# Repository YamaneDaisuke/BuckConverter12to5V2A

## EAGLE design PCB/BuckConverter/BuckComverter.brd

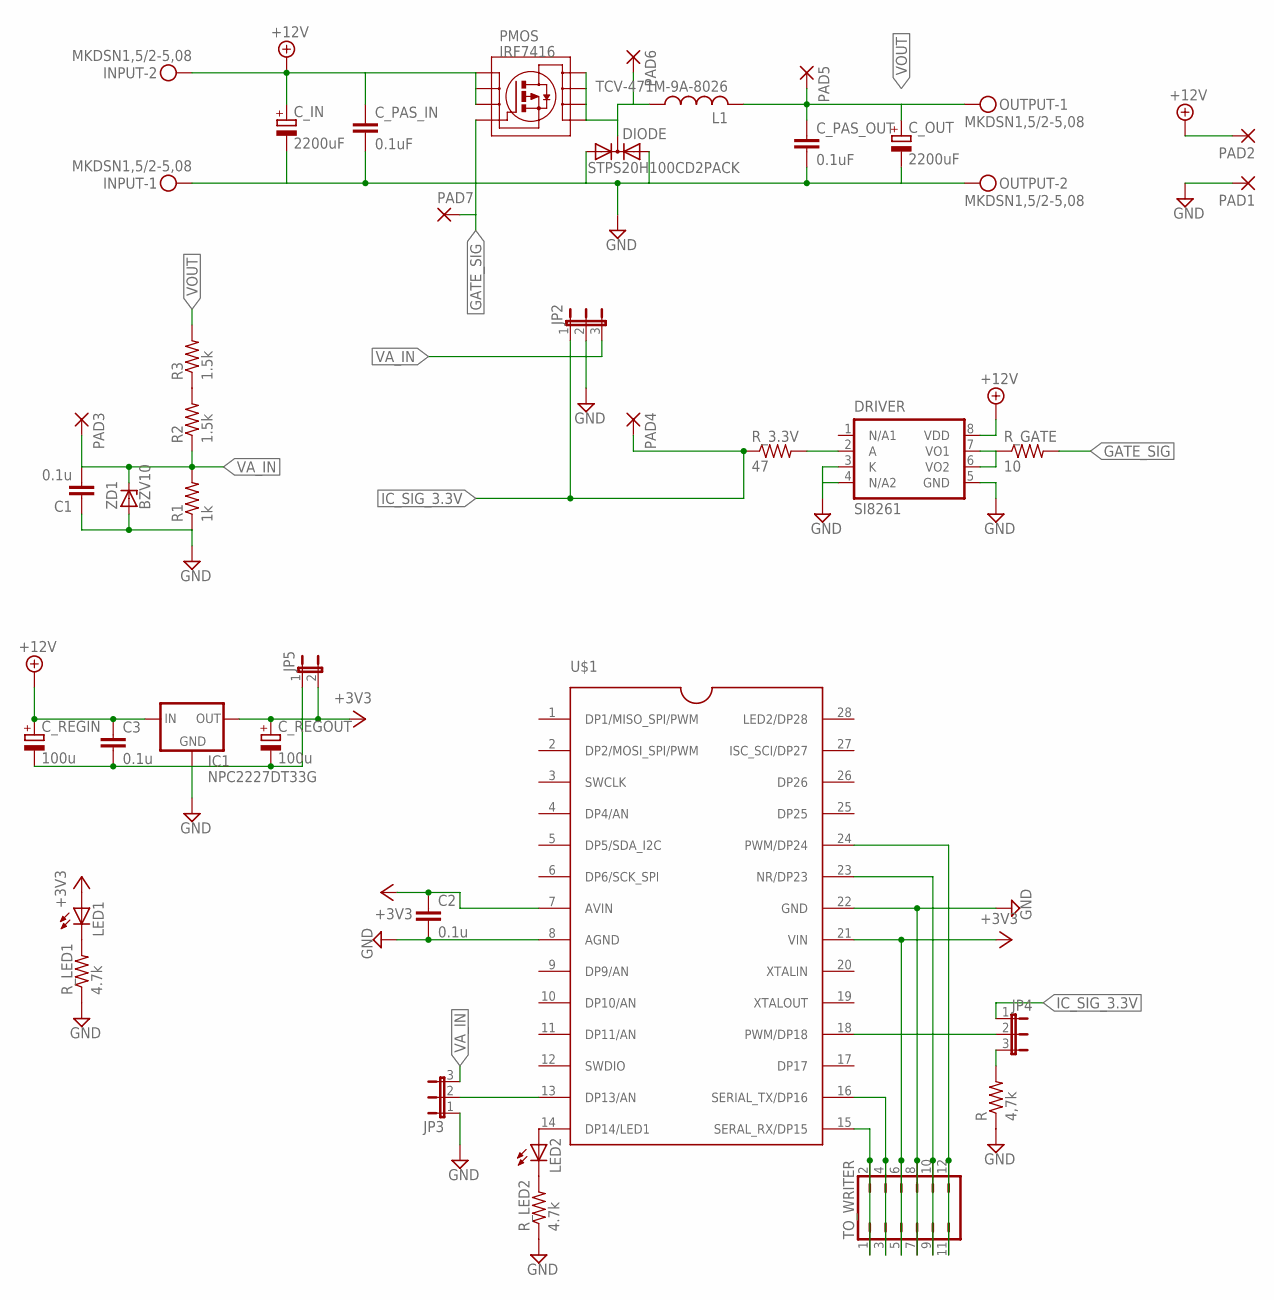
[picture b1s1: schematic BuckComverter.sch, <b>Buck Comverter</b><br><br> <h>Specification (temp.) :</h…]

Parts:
C1, C3: 0.1u; C025-024X044
C2: 0.1u; C2012
C_IN: 2200uF; E7,5-16
C_OUT: 2200uF; E7,5-16
C_PAS_IN: 0.1uF; C3216
C_PAS_OUT: 0.1uF; C3216
C_REGIN: 100u; E2,5-6
C_REGOUT: 100u; E2,5-6
DIODE: STPS20H100CD2PACK; D2PACK
DRIVER: SI8261; SOP08
IC1: NPC2227DT33G; DPACK
INPUT: MKDSN1,5/2-5,08
JP2, JP3, JP4: JP2E; JP2
JP5: JP1E; JP1
L1: TCV-471M-9A-8026
LED1, LED2: LED3MM
OUTPUT: MKDSN1,5/2-5,08
PAD1, PAD2, PAD3, PAD4, PAD5, PAD6, PAD7: 1,6/0,8
PMOS: IRF7416; SOP08
R: 4,7k; 0204/5
R1: 1k; 0207/7
R2: 1.5k; 0207/10
R3: 1.5k; 0207/7
R_3.3V: 47; 0204/7
R_GATE: 10; M2012
R_LED1: 4.7k; 0204V
R_LED2: 4.7k; 0204/7
TO_WRITER: JP6Q
U$1: LPC1114FDH28; TSSOP28
ZD1: BZV10; DO34Z7

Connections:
+3V3: C2.1, C_REGOUT.+, IC1.4 (OUT), JP5.2, LED1.A, TO_WRITER.5, TO_WRITER.6, U$1.7 (AVIN), U$1.21 (VIN)
+12V: C3.1, C_IN.+, C_PAS_IN.1, C_REGIN.+, DRIVER.8 (VDD), IC1.3 (IN), INPUT.2, PAD2.1, PMOS.1 (S1), PMOS.2 (S2), PMOS.3 (S3)
GATE_SIG: PAD7.1, PMOS.4 (G), R_GATE.2
GND: C1.1, C2.2, C3.2, C_IN.-, C_OUT.-, C_PAS_IN.2, C_PAS_OUT.2, C_REGIN.-, C_REGOUT.-, DIODE.1 (A3), DIODE.3 (A4), DRIVER.3 (K), DRIVER.4 (N/A2), DRIVER.5 (GND), IC1.1 (GND), INPUT.1, JP2.2, JP3.1, JP5.1, OUTPUT.2, PAD1.1, R.1, R1.1, R_LED1.1, R_LED2.1, TO_WRITER.7, TO_WRITER.8, U$1.8 (AGND), U$1.22 (GND), ZD1.A
IC_SIG_3.3V: JP2.1, JP4.1, PAD4.1, R_3.3V.1
unnamed: LED1.K (C), R_LED1.2
unnamed: DRIVER.2 (A), R_3.3V.2
unnamed: LED2.A, U$1.14 (DP14/LED1)
unnamed: R2.2, R3.1
unnamed: DRIVER.6 (VO2), DRIVER.7 (VO1), R_GATE.1
unnamed: JP3.2, U$1.13 (DP13/AN)
unnamed: JP4.3, R.2
unnamed: JP4.2, U$1.18 (PWM/DP18)
unnamed: TO_WRITER.1, TO_WRITER.2, U$1.15 (SERAL_RX/DP15)
unnamed: TO_WRITER.3, TO_WRITER.4, U$1.16 (SERIAL_TX/DP16)
unnamed: TO_WRITER.9, TO_WRITER.10, U$1.23 (NR/DP23)
unnamed: TO_WRITER.11, TO_WRITER.12, U$1.24 (PWM/DP24)
unnamed: LED2.K (C), R_LED2.2
unnamed: DIODE.2 (C), L1.P$1 (1), PAD6.1, PMOS.5 (D5), PMOS.6 (D6), PMOS.7 (D7), PMOS.8 (D8)
VA_IN: C1.2, JP2.3, JP3.3, PAD3.1, R1.2, R2.1, ZD1.C
VOUT: C_OUT.+, C_PAS_OUT.1, L1.P$2 (2), OUTPUT.1, PAD5.1, R3.2

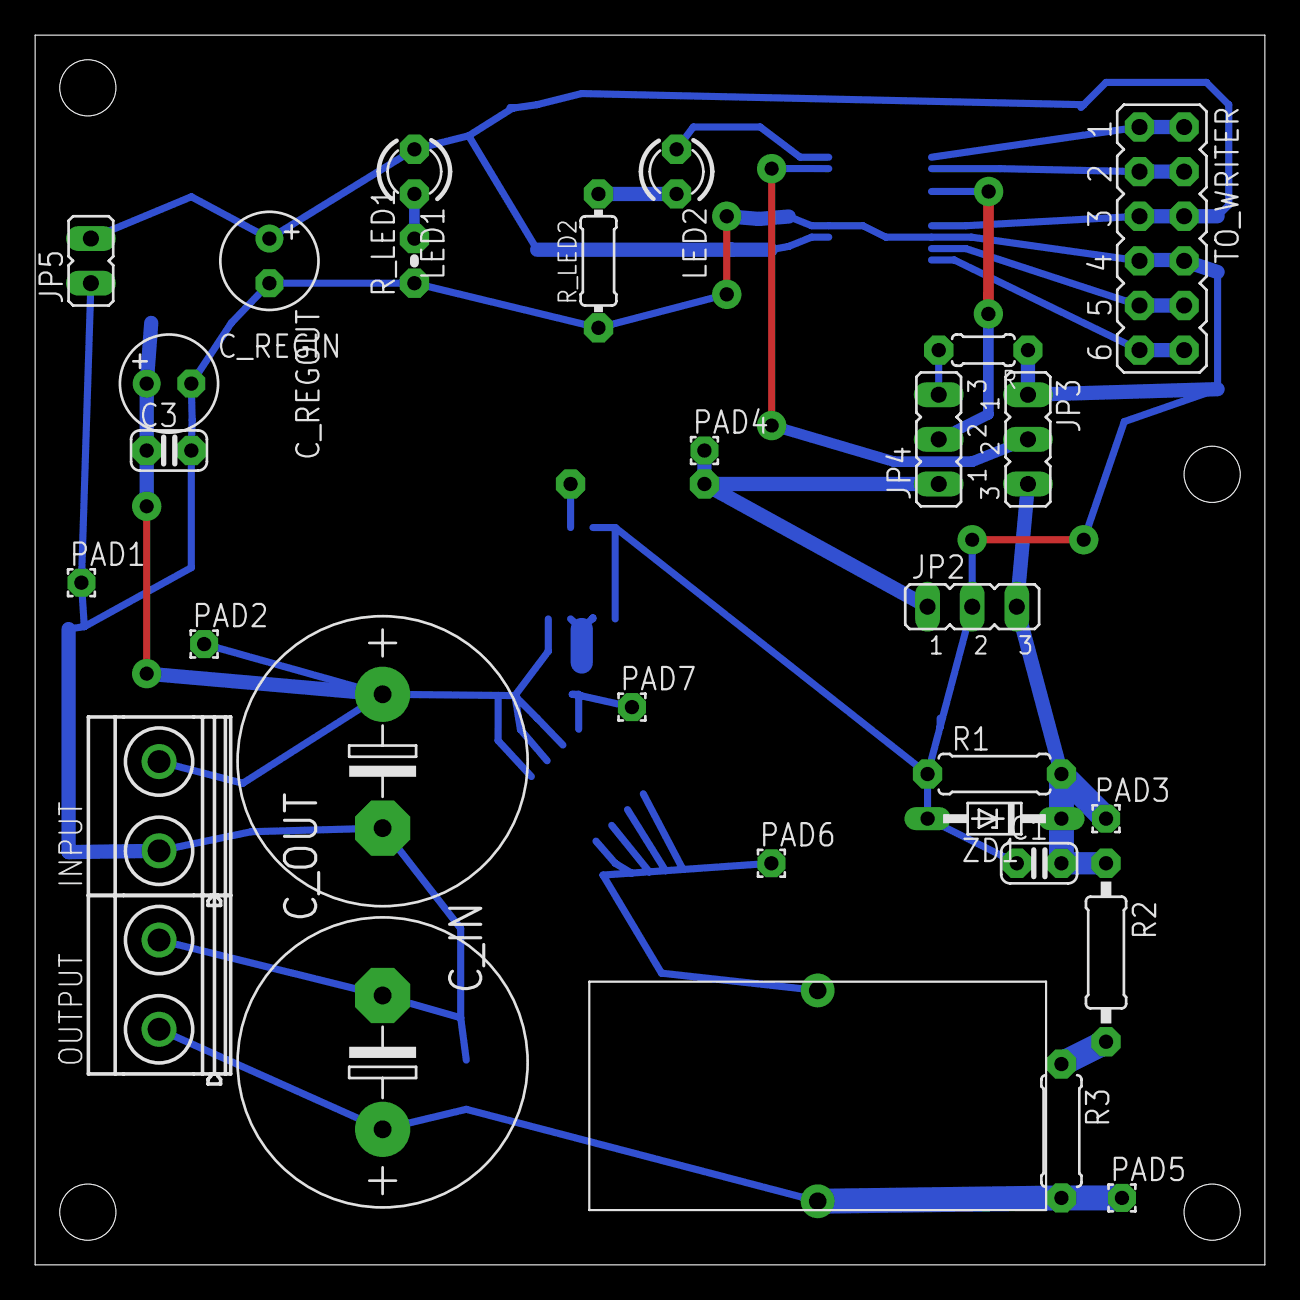
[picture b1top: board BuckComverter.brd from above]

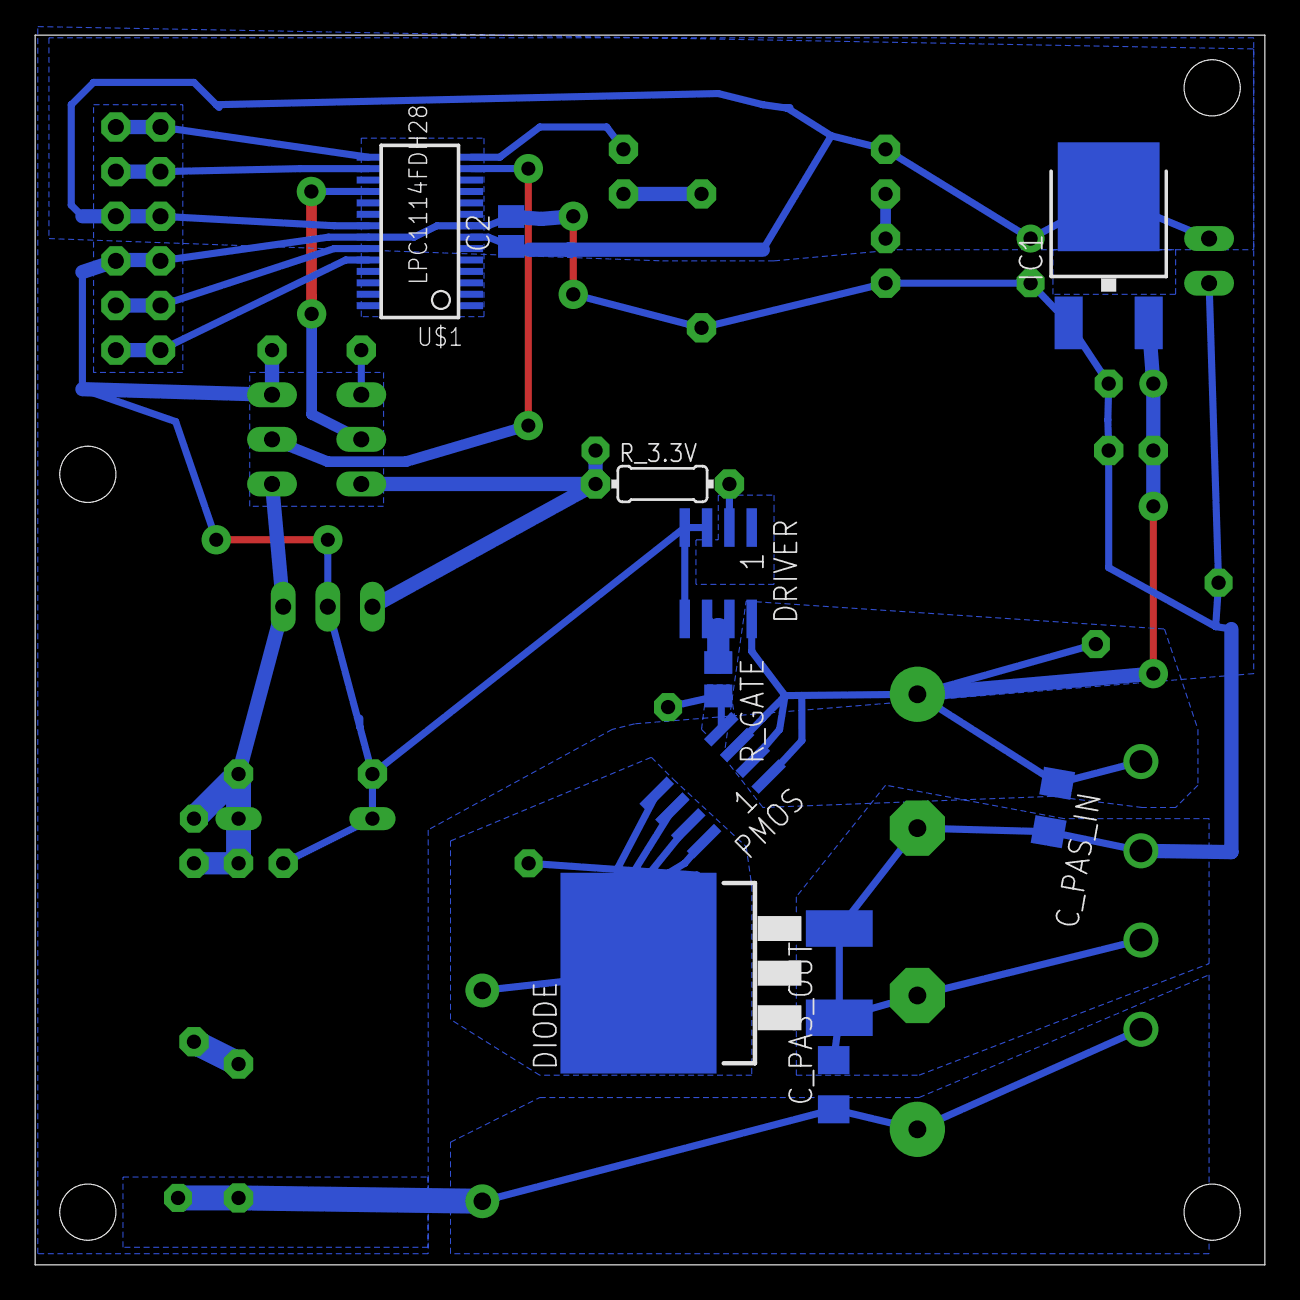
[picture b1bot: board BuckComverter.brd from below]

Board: 2 copper layers, 70.0 x 70.0 mm, 40 parts (10 on the bottom side), 21 nets.

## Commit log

2016-11-17 ADD gitignore
2016-11-22 ADD Eagle parts libraries
2016-11-22 降圧チョッパ回路の完成
2016-11-26 PIDコントローラの作成
2016-11-28 テストパッドを追加
2016-11-28 データシートを追加
2016-11-28 穴径を0.8, 1.0, 1.5, 3.2mmに統一
2016-11-29 TMS320F2807xのマニュアルを追加
2016-12-06 レギュレータライブラリ(v-reg2.lbr)にNPC1117DT33Gを追加
2016-12-06 回路のミスを修正
    修正内容：
    レギュレータのピン配置を修正
    PMOSの配線を修正
    上記に伴い、パターンの再設計
2016-12-13 ライブラリのランド形状を大きくした
2016-12-13 回路を改良
    詳細:
    殆どの信号線を0.016 -> 0.032 inch に変更
    ゲート周りの回路の最適化
    制御回路の電源ラインの最適化
    一部パーツの形状を変更
2016-12-22 Add Datasheets
